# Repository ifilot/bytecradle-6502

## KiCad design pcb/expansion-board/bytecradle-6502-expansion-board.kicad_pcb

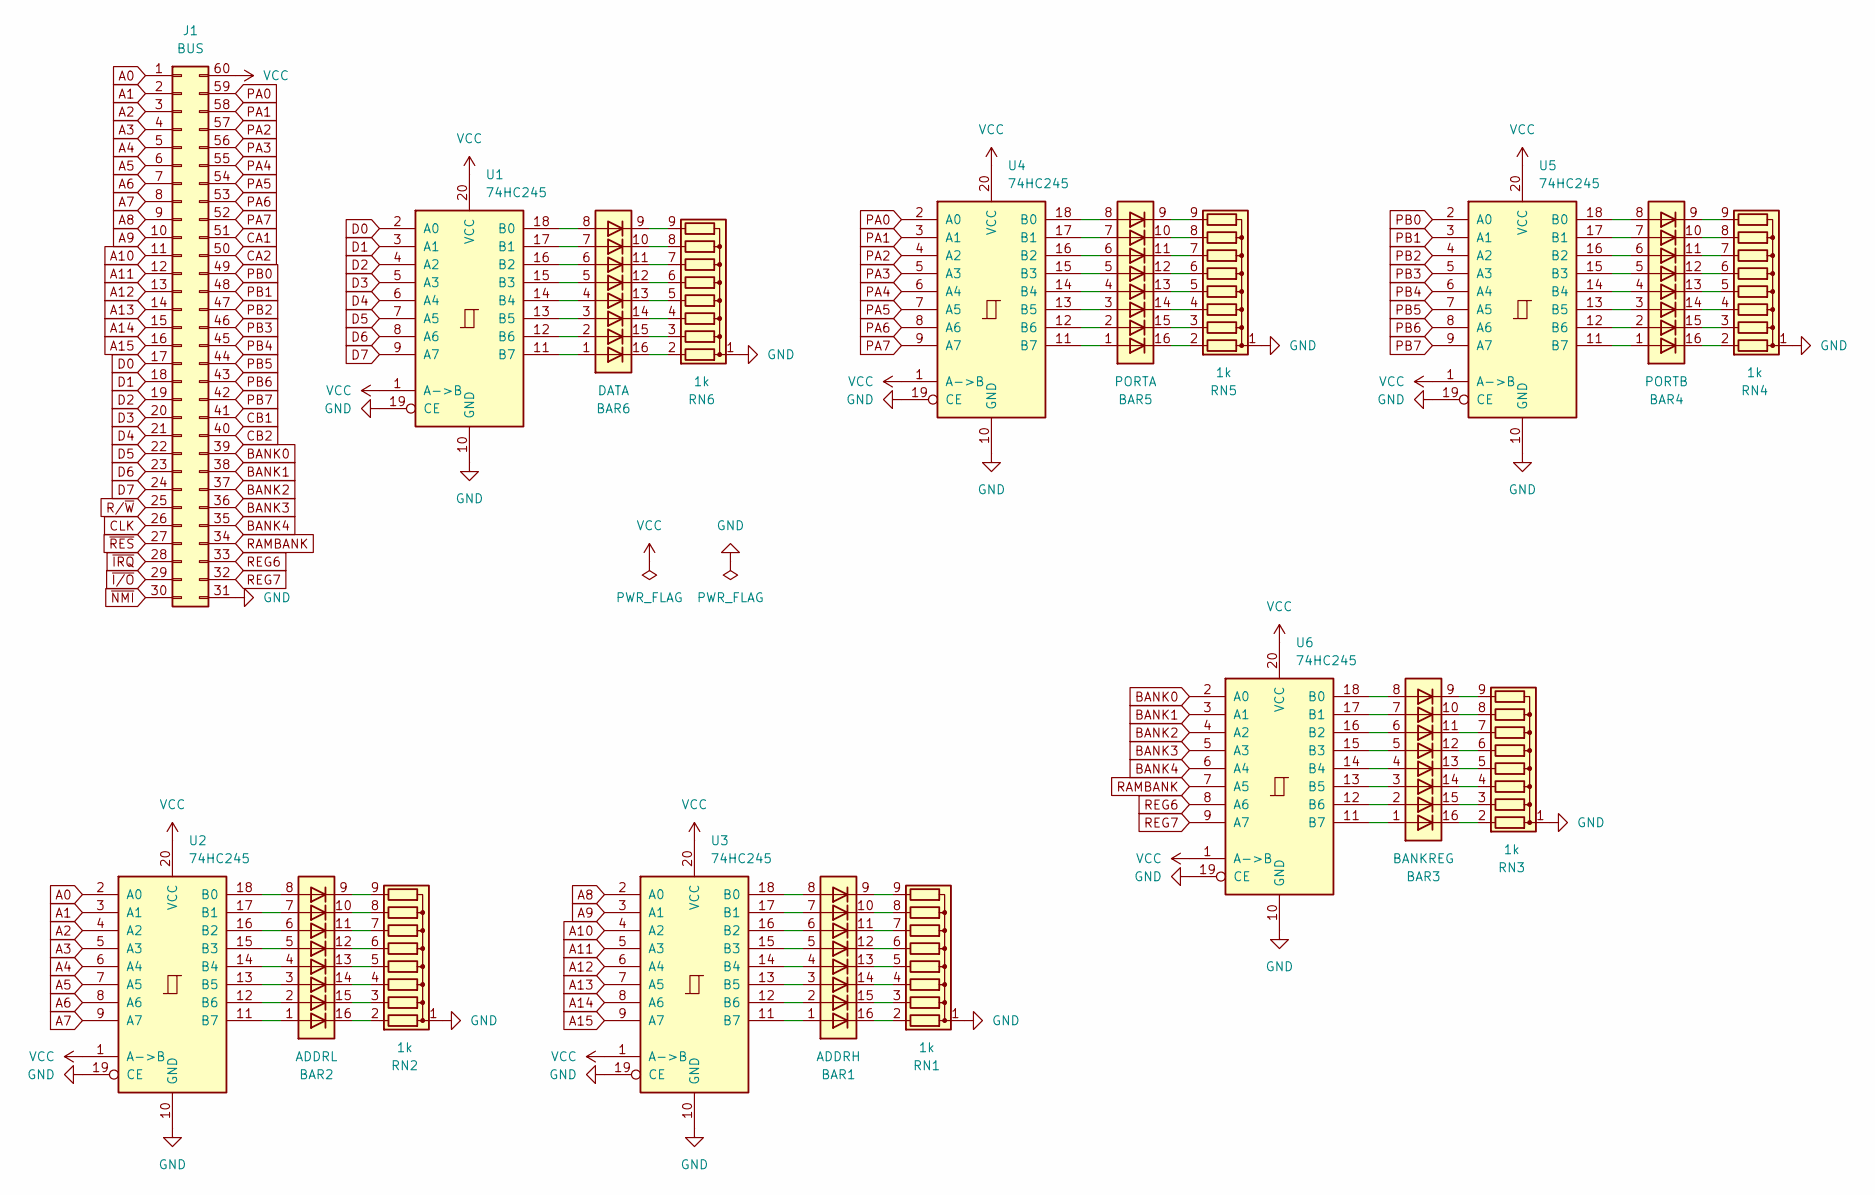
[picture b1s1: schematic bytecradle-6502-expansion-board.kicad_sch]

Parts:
BAR1: ADDRH; bargraph8
BAR2: ADDRL; bargraph8
BAR3: BANKREG; bargraph8
BAR4: PORTB; bargraph8
BAR5: PORTA; bargraph8
BAR6: DATA; bargraph8
J1: BUS; edge-connector-2x30
RN1, RN2, RN3, RN4, RN5, RN6: 1k; R_Array_SIP9
U1, U2, U3, U4, U5, U6: 74HC245; SOIC-20W_7.5x12.8mm_P1.27mm

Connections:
A0: J1.1, U2.2 (A0)
A1: J1.2, U2.3 (A1)
A2: J1.3, U2.4 (A2)
A3: J1.4, U2.5 (A3)
A4: J1.5, U2.6 (A4)
A5: J1.6, U2.7 (A5)
A6: J1.7, U2.8 (A6)
A7: J1.8, U2.9 (A7)
A8: J1.9, U3.2 (A0)
A9: J1.10, U3.3 (A1)
A10: J1.11, U3.4 (A2)
A11: J1.12, U3.5 (A3)
A12: J1.13, U3.6 (A4)
A13: J1.14, U3.7 (A5)
A14: J1.15, U3.8 (A6)
A15: J1.16, U3.9 (A7)
BANK0: J1.39, U6.2 (A0)
BANK1: J1.38, U6.3 (A1)
BANK2: J1.37, U6.4 (A2)
BANK3: J1.36, U6.5 (A3)
BANK4: J1.35, U6.6 (A4)
CA1: J1.51
CA2: J1.50
CB1: J1.41
CB2: J1.40
CLK: J1.26
D0: J1.17, U1.2 (A0)
D1: J1.18, U1.3 (A1)
D2: J1.19, U1.4 (A2)
D3: J1.20, U1.5 (A3)
D4: J1.21, U1.6 (A4)
D5: J1.22, U1.7 (A5)
D6: J1.23, U1.8 (A6)
D7: J1.24, U1.9 (A7)
GND: J1.31, RN1.1 (common), RN2.1 (common), RN3.1 (common), RN4.1 (common), RN5.1 (common), RN6.1 (common), U1.10 (GND), U1.19 (CE), U2.10 (GND), U2.19 (CE), U3.10 (GND), U3.19 (CE), U4.10 (GND), U4.19 (CE), U5.10 (GND), U5.19 (CE), U6.10 (GND), U6.19 (CE)
unnamed: BAR1.16 (K), RN1.2 (R1)
unnamed: BAR1.15 (K), RN1.3 (R2)
unnamed: BAR1.14 (K), RN1.4 (R3)
unnamed: BAR1.13 (K), RN1.5 (R4)
unnamed: BAR1.12 (K), RN1.6 (R5)
unnamed: BAR1.11 (K), RN1.7 (R6)
unnamed: BAR1.10 (K), RN1.8 (R7)
unnamed: BAR1.9 (K), RN1.9 (R8)
unnamed: BAR2.16 (K), RN2.2 (R1)
unnamed: BAR2.15 (K), RN2.3 (R2)
unnamed: BAR2.14 (K), RN2.4 (R3)
unnamed: BAR2.13 (K), RN2.5 (R4)
unnamed: BAR2.12 (K), RN2.6 (R5)
unnamed: BAR2.11 (K), RN2.7 (R6)
unnamed: BAR2.10 (K), RN2.8 (R7)
unnamed: BAR2.9 (K), RN2.9 (R8)
unnamed: BAR3.16 (K), RN3.2 (R1)
unnamed: BAR3.15 (K), RN3.3 (R2)
unnamed: BAR3.14 (K), RN3.4 (R3)
unnamed: BAR3.13 (K), RN3.5 (R4)
unnamed: BAR3.12 (K), RN3.6 (R5)
unnamed: BAR3.11 (K), RN3.7 (R6)
unnamed: BAR3.10 (K), RN3.8 (R7)
unnamed: BAR3.9 (K), RN3.9 (R8)
unnamed: BAR4.16 (K), RN4.2 (R1)
unnamed: BAR4.15 (K), RN4.3 (R2)
unnamed: BAR4.14 (K), RN4.4 (R3)
unnamed: BAR4.13 (K), RN4.5 (R4)
unnamed: BAR4.12 (K), RN4.6 (R5)
unnamed: BAR4.11 (K), RN4.7 (R6)
unnamed: BAR4.10 (K), RN4.8 (R7)
unnamed: BAR4.9 (K), RN4.9 (R8)
unnamed: BAR5.16 (K), RN5.2 (R1)
unnamed: BAR5.15 (K), RN5.3 (R2)
unnamed: BAR5.14 (K), RN5.4 (R3)
unnamed: BAR5.13 (K), RN5.5 (R4)
unnamed: BAR5.12 (K), RN5.6 (R5)
unnamed: BAR5.11 (K), RN5.7 (R6)
unnamed: BAR5.10 (K), RN5.8 (R7)
unnamed: BAR5.9 (K), RN5.9 (R8)
unnamed: BAR6.16 (K), RN6.2 (R1)
unnamed: BAR6.15 (K), RN6.3 (R2)
unnamed: BAR6.14 (K), RN6.4 (R3)
unnamed: BAR6.13 (K), RN6.5 (R4)
unnamed: BAR6.12 (K), RN6.6 (R5)
unnamed: BAR6.11 (K), RN6.7 (R6)
unnamed: BAR6.10 (K), RN6.8 (R7)
unnamed: BAR6.9 (K), RN6.9 (R8)
unnamed: BAR6.8 (A), U1.18 (B0)
unnamed: BAR6.7 (A), U1.17 (B1)
unnamed: BAR6.6 (A), U1.16 (B2)
unnamed: BAR6.5 (A), U1.15 (B3)
unnamed: BAR6.4 (A), U1.14 (B4)
unnamed: BAR6.3 (A), U1.13 (B5)
unnamed: BAR6.2 (A), U1.12 (B6)
unnamed: BAR6.1 (A), U1.11 (B7)
unnamed: BAR2.8 (A), U2.18 (B0)
unnamed: BAR2.7 (A), U2.17 (B1)
unnamed: BAR2.6 (A), U2.16 (B2)
unnamed: BAR2.5 (A), U2.15 (B3)
unnamed: BAR2.4 (A), U2.14 (B4)
unnamed: BAR2.3 (A), U2.13 (B5)
unnamed: BAR2.2 (A), U2.12 (B6)
unnamed: BAR2.1 (A), U2.11 (B7)
unnamed: BAR1.8 (A), U3.18 (B0)
unnamed: BAR1.7 (A), U3.17 (B1)
unnamed: BAR1.6 (A), U3.16 (B2)
unnamed: BAR1.5 (A), U3.15 (B3)
unnamed: BAR1.4 (A), U3.14 (B4)
unnamed: BAR1.3 (A), U3.13 (B5)
unnamed: BAR1.2 (A), U3.12 (B6)
unnamed: BAR1.1 (A), U3.11 (B7)
unnamed: BAR5.8 (A), U4.18 (B0)
unnamed: BAR5.7 (A), U4.17 (B1)
unnamed: BAR5.6 (A), U4.16 (B2)
unnamed: BAR5.5 (A), U4.15 (B3)
unnamed: BAR5.4 (A), U4.14 (B4)
unnamed: BAR5.3 (A), U4.13 (B5)
unnamed: BAR5.2 (A), U4.12 (B6)
unnamed: BAR5.1 (A), U4.11 (B7)
unnamed: BAR4.8 (A), U5.18 (B0)
unnamed: BAR4.7 (A), U5.17 (B1)
unnamed: BAR4.6 (A), U5.16 (B2)
unnamed: BAR4.5 (A), U5.15 (B3)
unnamed: BAR4.4 (A), U5.14 (B4)
unnamed: BAR4.3 (A), U5.13 (B5)
unnamed: BAR4.2 (A), U5.12 (B6)
unnamed: BAR4.1 (A), U5.11 (B7)
unnamed: BAR3.8 (A), U6.18 (B0)
unnamed: BAR3.7 (A), U6.17 (B1)
unnamed: BAR3.6 (A), U6.16 (B2)
unnamed: BAR3.5 (A), U6.15 (B3)
unnamed: BAR3.4 (A), U6.14 (B4)
unnamed: BAR3.3 (A), U6.13 (B5)
unnamed: BAR3.2 (A), U6.12 (B6)
unnamed: BAR3.1 (A), U6.11 (B7)
PA0: J1.59, U4.2 (A0)
PA1: J1.58, U4.3 (A1)
PA2: J1.57, U4.4 (A2)
PA3: J1.56, U4.5 (A3)
PA4: J1.55, U4.6 (A4)
PA5: J1.54, U4.7 (A5)
PA6: J1.53, U4.8 (A6)
PA7: J1.52, U4.9 (A7)
PB0: J1.49, U5.2 (A0)
PB1: J1.48, U5.3 (A1)
PB2: J1.47, U5.4 (A2)
PB3: J1.46, U5.5 (A3)
PB4: J1.45, U5.6 (A4)
PB5: J1.44, U5.7 (A5)
PB6: J1.43, U5.8 (A6)
PB7: J1.42, U5.9 (A7)
RAMBANK: J1.34, U6.7 (A5)
REG6: J1.33, U6.8 (A6)
REG7: J1.32, U6.9 (A7)
R/~W: J1.25
VCC: J1.60, U1.1 (A->B), U1.20 (VCC), U2.1 (A->B), U2.20 (VCC), U3.1 (A->B), U3.20 (VCC), U4.1 (A->B), U4.20 (VCC), U5.1 (A->B), U5.20 (VCC), U6.1 (A->B), U6.20 (VCC)
~IRQ: J1.28
~I/O: J1.29
~NMI: J1.30
~RES: J1.27

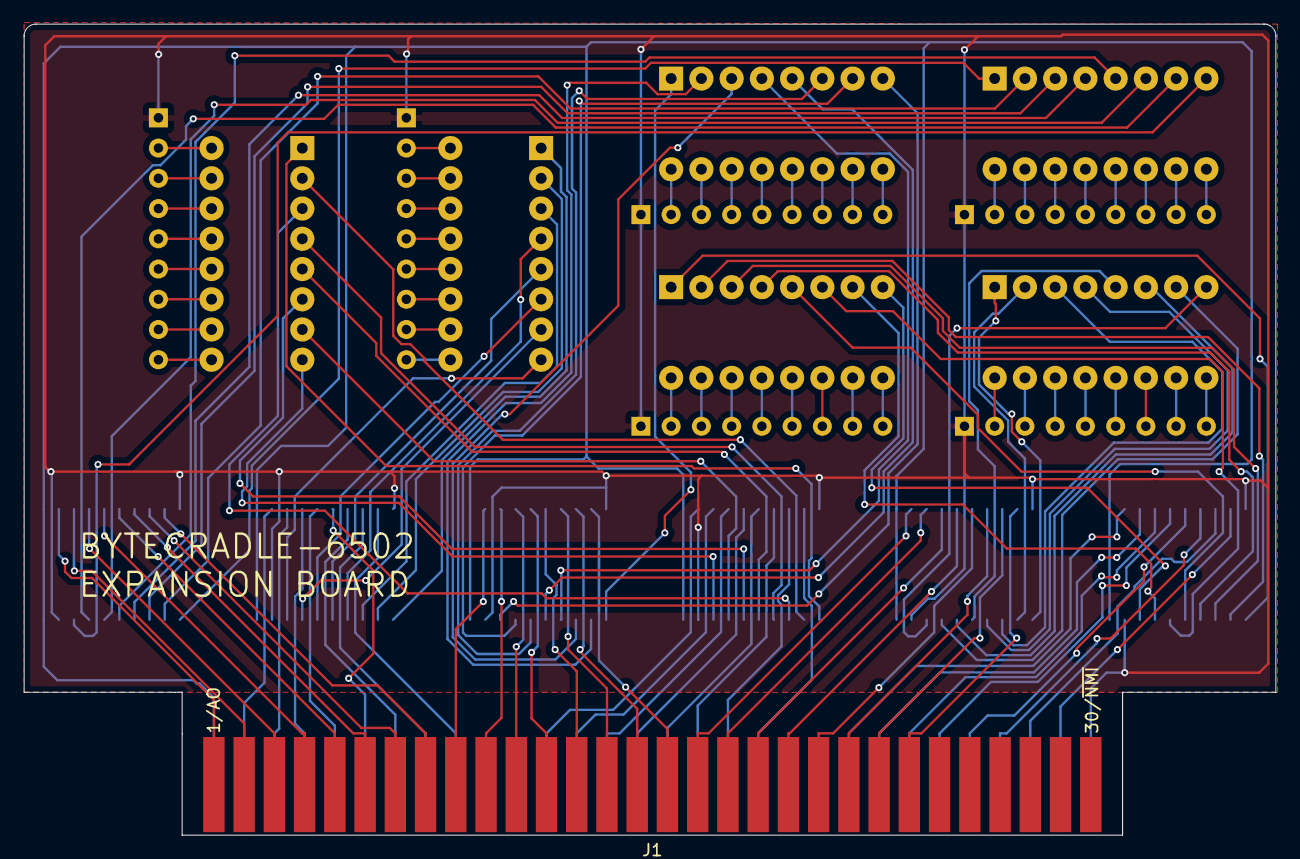
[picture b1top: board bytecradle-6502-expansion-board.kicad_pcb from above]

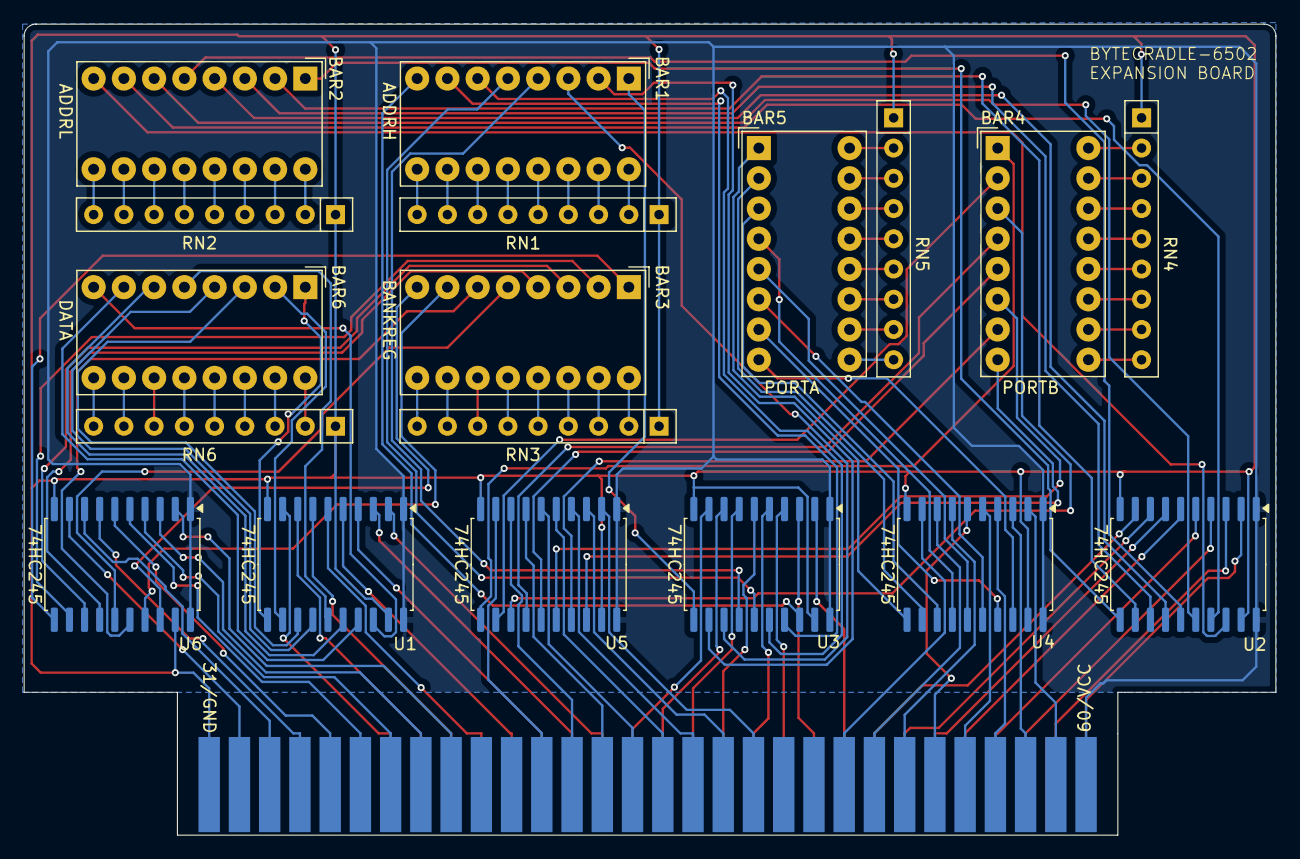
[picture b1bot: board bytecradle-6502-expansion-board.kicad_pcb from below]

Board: 2 copper layers, 105.2 x 68.1 mm, 19 parts (18 on the bottom side), 146 nets.
